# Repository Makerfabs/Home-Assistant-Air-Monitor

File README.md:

# Makerfabs Home Assistant Air Monitor

## Intruduce

[Product Link]()

[Wiki Link]()

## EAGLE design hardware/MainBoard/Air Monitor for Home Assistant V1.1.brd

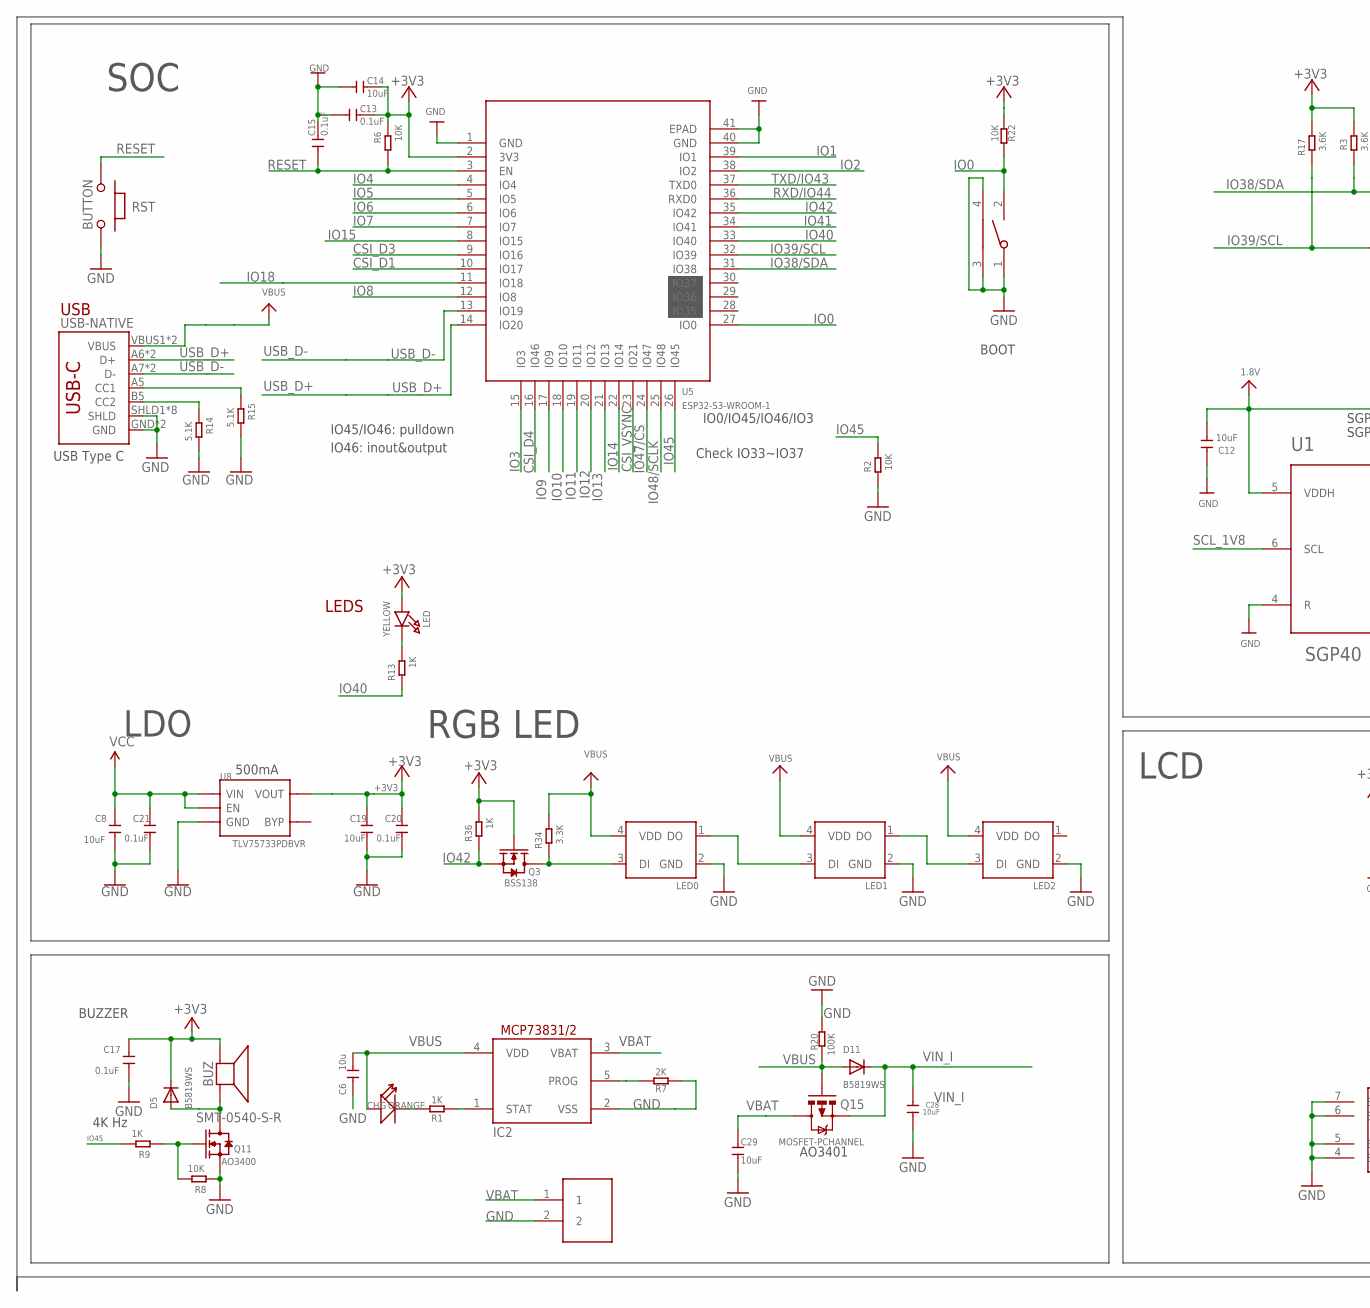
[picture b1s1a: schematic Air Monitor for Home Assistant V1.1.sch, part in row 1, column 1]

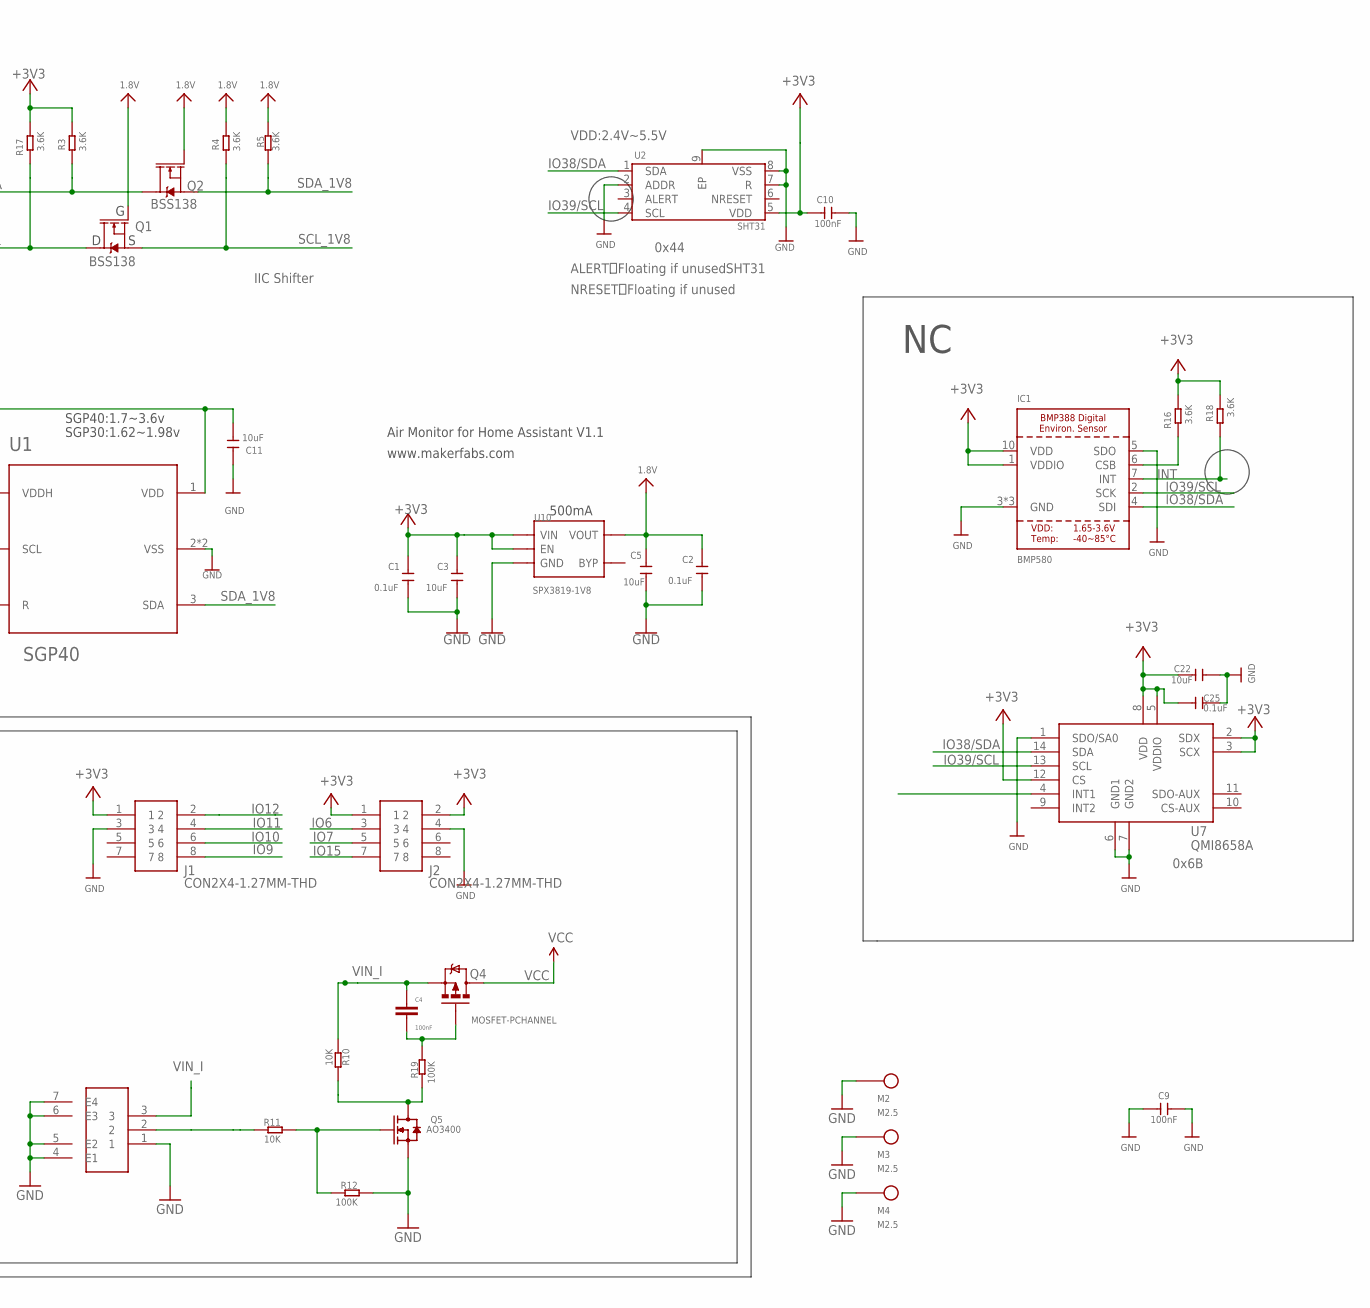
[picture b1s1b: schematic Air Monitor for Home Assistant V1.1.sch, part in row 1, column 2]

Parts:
BAT: PH2.0-2P-90-DIP
BOOT: TS24CA; 2*4*3.5MM
BUZ: SMT-0540-S-R
C1, C2, C13, C15, C17, C20, C21, C25: 0.1uF; DISCRETE_C0402
C3, C5, C8, C14, C19, C22: 10uF; DISCRETE_C0402
C4: 100nF; C0603
C6: 10u; 0603
C9, C10: 100nF; 0603
C11, C12, C28, C29: 10uF; 0603
CHG: ORANGE; D0603
D5, D11: B5819WS; SOD-323F
IC1: BMP580; BMP388
IC2: MCP73831/OT; SOT23-5L
J1, J2: CON2X4-1.27MM-THD
LED: YELLOW; CHIPLED_0805_NOOUTLINE
LED0, LED1, LED2: WS2812B-2020
M2, M3, M4: M2.5
Q1, Q2: BSS138; SOT23-3
Q3: BSS138; SOT23
Q4, Q15: MOSFET-PCHANNEL; SOT23-3
Q5, Q11: AO3400; SOT23
R1, R9, R13, R36: 1K; DISCRETE_R0402
R2, R6, R8, R10, R11, R22: 10K; DISCRETE_R0402
R3, R4, R5, R16, R17, R18: 3.6K; DISCRETE_R0402
R7: 2K; DISCRETE_R0402
R12, R19, R20: 100K; DISCRETE_R0402
R14, R15: 5.1K; DISCRETE_R0402
R34: 3.3K; DISCRETE_R0402
RST: BUTTON; 157SW
SW1: SWITCH02B
U1: SGP40; SGP30
U2: SHT31; DFN-8(3X3)_EP
U5: ESP32-S3-WROOM-1
U7: QMI8658A; LGA14-50P-300L250W86H
U8: TLV75733PDBVR; SOT23-5
U10: SPX3819-1V8; SOT23-5
USB-NATIVE: USB_C5; USB-C-16P-5

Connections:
1.8V: C2.2, C5.2, C11.1, C12.1, Q1.1 (G), Q2.1 (G), R4.2, R5.2, U1.1 (VDD), U1.5 (VDDH), U10.5 (VOUT)
+3V3: BUZ.+ (-), C1.2, C3.2, C10.1, C13.1, C14.1, C17.2, C19.2, C20.2, C22.2, C25.2, D5.C, IC1.1 (VDDIO), IC1.10 (VDD), J1.1, J2.1, J2.2, LED.A, Q3.1 (G), R3.2, R6.2, R16.2, R17.2, R18.2, R22.1, R36.2, U2.5 (VDD), U5.2 (3V3), U7.2 (SDX), U7.3 (SCX), U7.5 (VDDIO), U7.8 (VDD), U7.12 (CS), U8.5 (VOUT), U10.1 (VIN), U10.3 (EN)
CSI_D1: U5.10 (IO17)
CSI_D3: U5.9 (IO16)
CSI_D4: U5.16 (IO46)
CSI_VSYNC: U5.23 (IO21)
GND: BAT.2, BOOT.1, BOOT.3, BOOT.4, C1.1, C2.1, C3.1, C5.1, C6.1, C8.1, C9.1, C9.2, C10.2, C11.2, C12.2, C13.2, C14.2, C15.1, C17.1, C19.1, C20.1, C21.1, C22.1, C25.1, C28.1, C29.2, IC1.3 (GND), IC1.5 (SDO), IC1.8 (GND), IC1.9 (GND), IC2.2 (VSS), J1.3, J2.4, LED0.2 (GND), LED1.2 (GND), LED2.2 (GND), M2.1, M3.1, M4.1, Q5.2 (S), Q11.2 (S), R2.1, R7.1, R8.1, R12.2, R14.2, R15.2, R20.2, RST.1, SW1.1, SW1.4 (E1), SW1.5 (E2), SW1.6 (E3), SW1.7 (E4), U1.2 (VSS), U1.4 (R), U1.P$7 (VSS), U2.2 (ADDR), U2.7 (R), U2.8 (VSS), U2.9 (EP), U5.1 (GND), U5.40 (GND), U5.41 (EPAD), U7.1 (SDO/SA0), U7.6 (GND1), U7.7 (GND2), U8.2 (GND), U10.2 (GND), USB-NATIVE.GND, USB-NATIVE.GND2 (GND), USB-NATIVE.SHLD1 (SHLD), USB-NATIVE.SHLD2 (SHLD), USB-NATIVE.SHLD3 (SHLD), USB-NATIVE.SHLD4 (SHLD), USB-NATIVE.SHLD5 (SHLD), USB-NATIVE.SHLD6 (SHLD), USB-NATIVE.SHLD7 (SHLD), USB-NATIVE.SHLD8 (SHLD)
INT: IC1.7 (INT), R18.1
IO0: BOOT.2, R22.2, U5.27 (IO0)
IO1: U5.39 (IO1)
IO2: U5.38 (IO2)
IO3: U5.15 (IO3)
IO4: U5.4 (IO4)
IO5: U5.5 (IO5)
IO6: J2.3, U5.6 (IO6)
IO7: J2.5, U5.7 (IO7)
IO8: U5.12 (IO8)
IO9: J1.8, U5.17 (IO9)
IO10: J1.6, U5.18 (IO10)
IO11: J1.4, U5.19 (IO11)
IO12: J1.2, U5.20 (IO12)
IO13: U5.21 (IO13)
IO14: U5.22 (IO14)
IO15: J2.7, U5.8 (IO15)
IO18: U5.11 (IO18)
IO38/SDA: IC1.4 (SDI), Q2.3 (D), R3.1, U2.1 (SDA), U5.31 (IO38), U7.14 (SDA)
IO39/SCL: IC1.2 (SCK), Q1.3 (D), R17.1, U2.4 (SCL), U5.32 (IO39), U7.13 (SCL)
IO40: R13.1, U5.33 (IO40)
IO41: U5.34 (IO41)
IO42: Q3.2 (S), R36.1, U5.35 (IO42)
IO45: R2.2, R9.2, U5.26 (IO45)
IO47/CS: U5.24 (IO47)
IO48/SCLK: U5.25 (IO48)
M-1: BUZ.- (+), D5.A, Q11.3 (D)
unnamed: IC1.6 (CSB), R16.1
unnamed: CHG.-, R1.2
unnamed: Q5.3 (D), R10.2, R19.1
unnamed: LED1.1 (DO), LED2.3 (DI)
unnamed: LED0.1 (DO), LED1.3 (DI)
unnamed: R11.1, SW1.2
unnamed: C4.2, Q4.1 (G), R19.2
unnamed: Q5.1 (G), R11.2, R12.1
unnamed: LED.C, R13.2
unnamed: LED0.3 (DI), Q3.3 (D), R34.1
unnamed: Q11.1 (G), R8.2, R9.1
unnamed: IC2.1 (STAT), R1.1
unnamed: IC2.5 (PROG), R7.2
unnamed: R15.1, USB-NATIVE.A5 (CC1)
unnamed: R14.1, USB-NATIVE.B5 (CC2)
RESET: C15.2, R6.1, RST.2, U5.3 (EN)
RXD/IO44: U5.36 (RXD0)
SCL_1V8: Q1.2 (S), R4.1, U1.6 (SCL)
SDA_1V8: Q2.2 (S), R5.1, U1.3 (SDA)
TXD/IO43: U5.37 (TXD0)
USB_D+: U5.14 (IO20), USB-NATIVE.A6 (D+), USB-NATIVE.B6 (D+)
USB_D-: U5.13 (IO19), USB-NATIVE.A7 (D-), USB-NATIVE.B7 (D-)
VBAT: BAT.1, C29.1, IC2.3 (VBAT), Q15.3 (D)
VBUS: C6.2, CHG.+, D11.A, IC2.4 (VDD), LED0.4 (VDD), LED1.4 (VDD), LED2.4 (VDD), Q15.1 (G), R20.1, R34.2, USB-NATIVE.VBUS1 (VBUS), USB-NATIVE.VBUS2 (VBUS)
VCC: C8.2, C21.2, Q4.3 (D), U8.1 (VIN), U8.3 (EN)
VIN_I: C4.1, C28.2, D11.C, Q4.2 (S), Q15.2 (S), R10.1, SW1.3

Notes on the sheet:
500mA
LDO
LEDS
BOOT
IO45/IO46: pulldown
IO46: inout&output
USB
USB Type C
IO0/IO45/IO46/IO3
Check IO33~IO37
SOC
BUZZER
4K Hz
RGB LED
SHT31
IIC Shifter
Air Monitor for Home Assistant V1.1
www.makerfabs.com
VDD:2.4V~5.5V
ALERT：Floating if unused
NRESET：Floating if unused
SGP40:1.7~3.6v
SGP30:1.62~1.98v
0x44
0x6B
LCD
AO3401

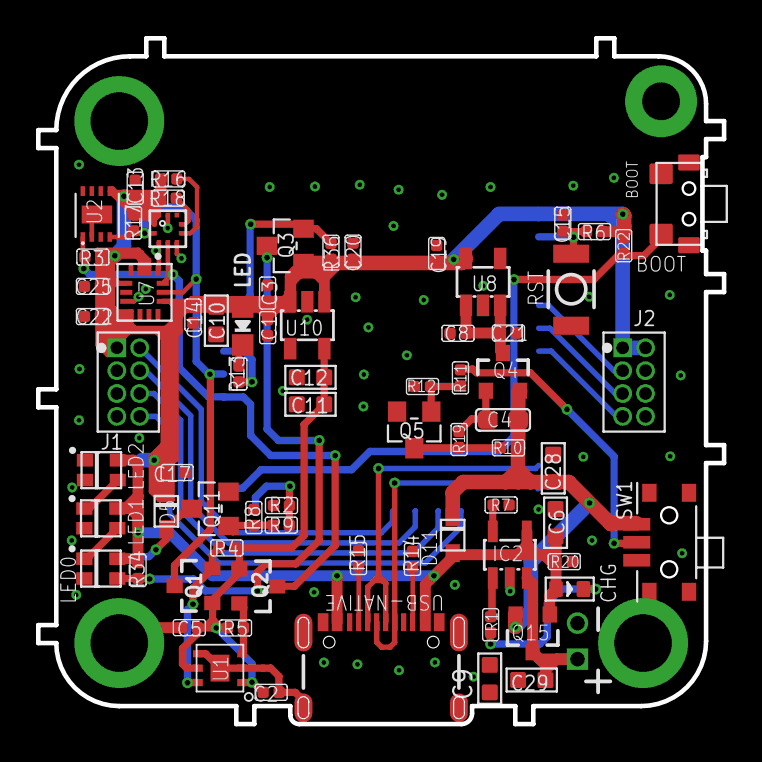
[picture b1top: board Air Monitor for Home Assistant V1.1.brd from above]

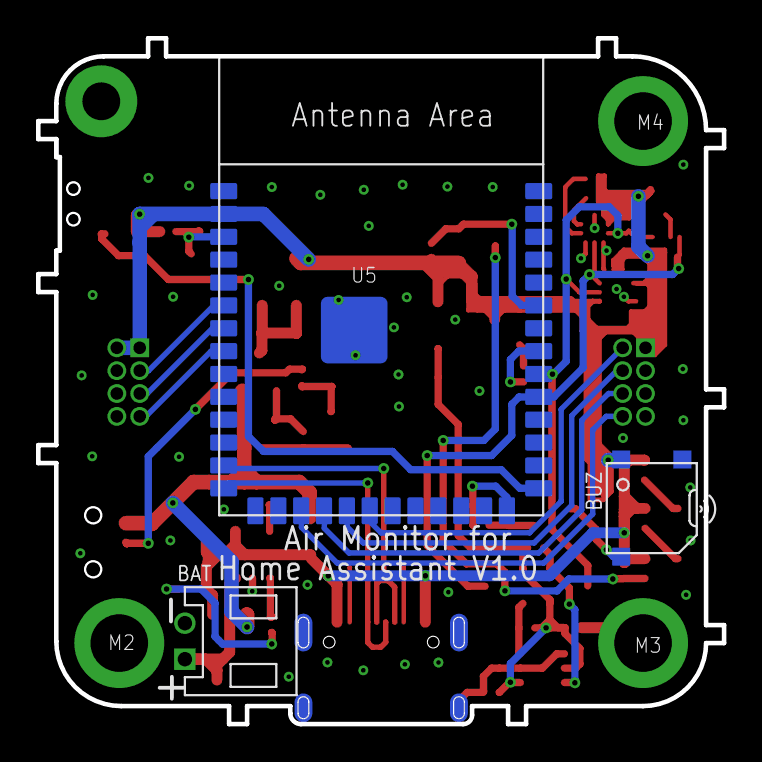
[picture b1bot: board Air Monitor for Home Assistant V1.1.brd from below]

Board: 2 copper layers, 38.1 x 38.1 mm, 78 parts (6 on the bottom side), 42 nets.

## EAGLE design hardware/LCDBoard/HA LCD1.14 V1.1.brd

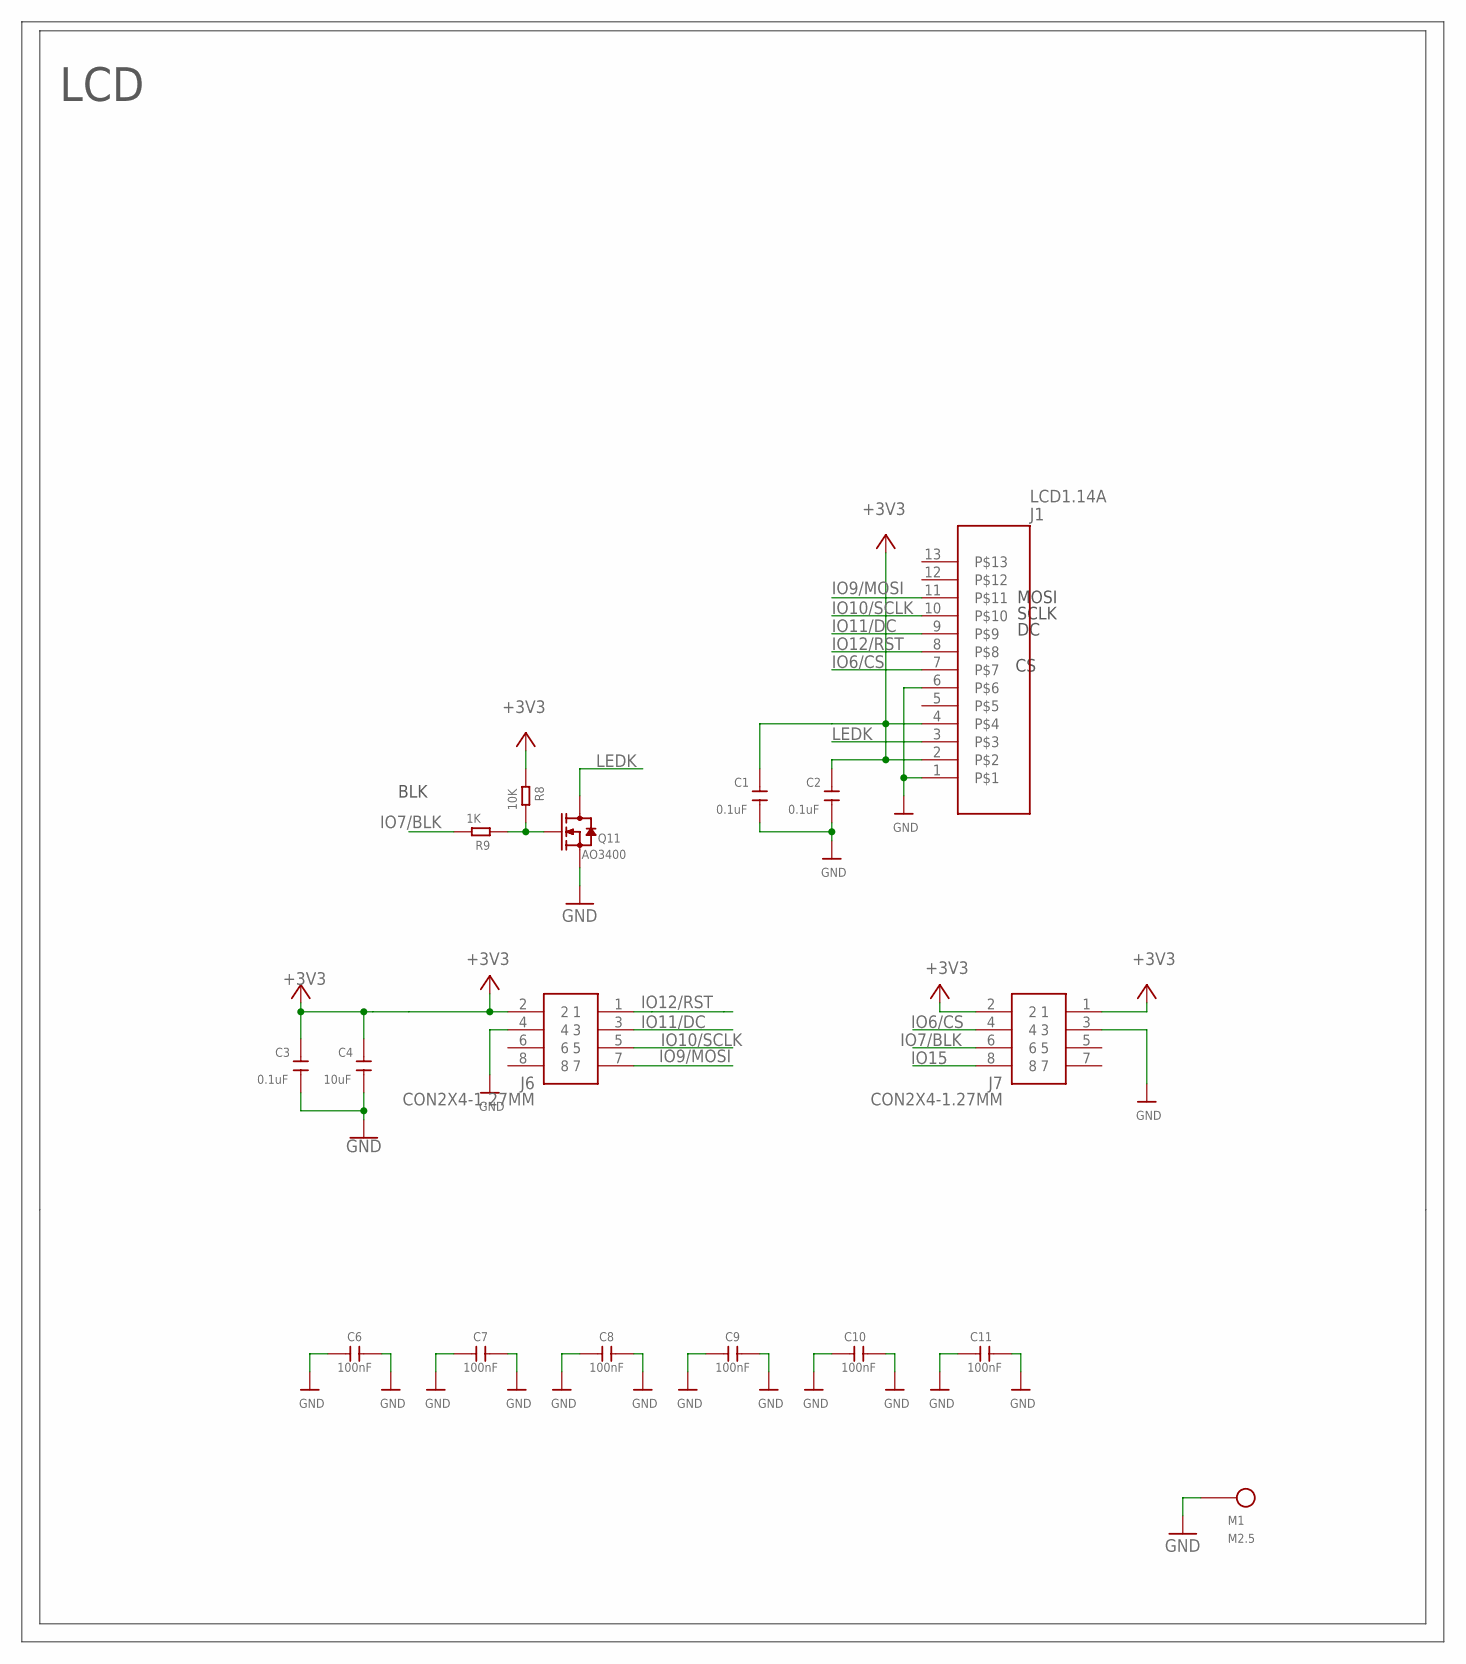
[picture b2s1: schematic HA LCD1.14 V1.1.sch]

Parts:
C1, C2, C3: 0.1uF; DISCRETE_C0402
C4: 10uF; DISCRETE_C0402
C6, C7, C8, C9, C10, C11: 100nF; 0603
J1: LCD1.14A
J6, J7: CON2X4-1.27MM
M1: M2.5
Q11: AO3400; SOT23
R8: 10K; DISCRETE_R0402
R9: 1K; DISCRETE_R0402

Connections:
+3V3: C1.2, C2.2, C3.2, C4.2, J1.2, J1.4, J6.2, J7.1, J7.2, R8.1
GND: C1.1, C2.1, C3.1, C4.1, C6.1, C6.2, C7.1, C7.2, C8.1, C8.2, C9.1, C9.2, C10.1, C10.2, C11.1, C11.2, J1.1, J1.6, J6.4, J7.3, M1.1, Q11.2 (S)
IO6/CS: J1.7, J7.4
IO7/BLK: J7.6, R9.2
IO9/MOSI: J1.11, J6.7
IO10/SCLK: J1.10, J6.5
IO11/DC: J1.9, J6.3
IO12/RST: J1.8, J6.1
IO15: J7.8
LEDK: J1.3, Q11.3 (D)
unnamed: Q11.1 (G), R8.2, R9.1

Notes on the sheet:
LCD
MOSI
SCLK
BLK

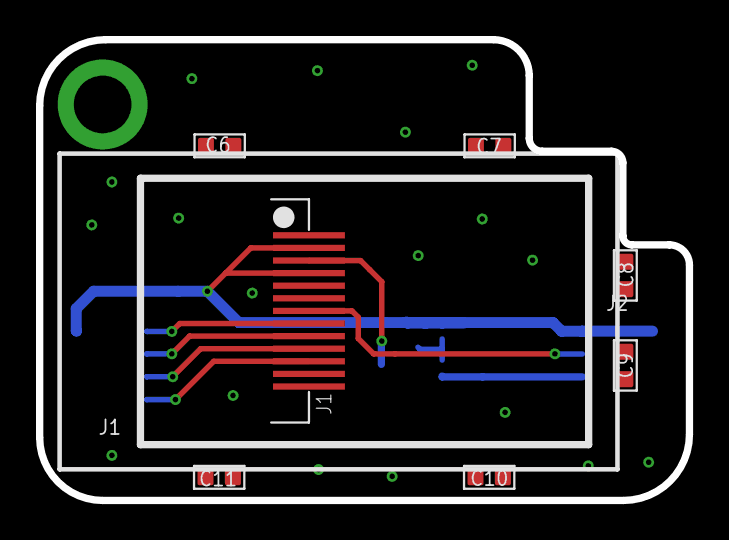
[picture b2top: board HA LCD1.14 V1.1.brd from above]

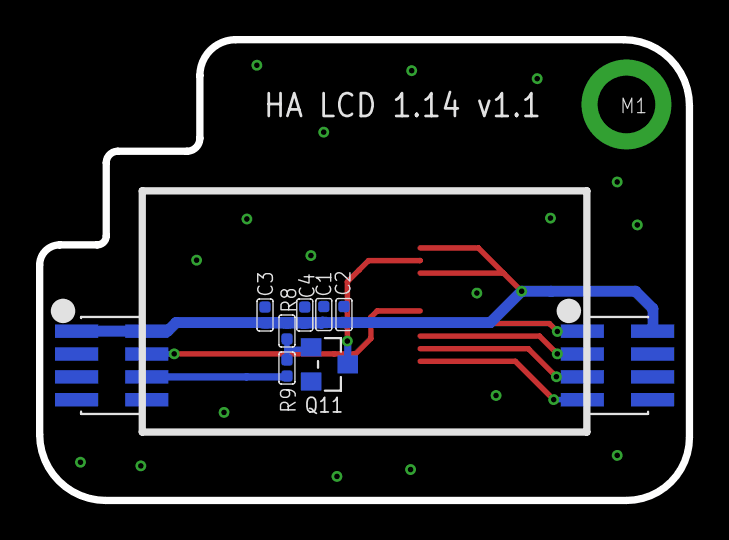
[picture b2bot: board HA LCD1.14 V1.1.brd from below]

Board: 2 copper layers, 36.1 x 25.6 mm, 17 parts (10 on the bottom side), 10 nets.

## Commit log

2026-01-23 add file
2026-01-28 update yaml
2026-01-28 del hardware

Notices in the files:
parts and their libraries:
microbuilder: This work is placed in the public domain, and may be freely used for commercial and non-commercial work with the following conditions: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
SparkFun-PowerSymbols: Licensing: Creative Commons ShareAlike 4.0 International - https://creativecommons.org/licenses/by-sa/4.0
